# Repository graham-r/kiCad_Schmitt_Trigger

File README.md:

# kiCad_Schmitt_Trigger
Schmitt Trigger switch-bounce removal based kiCad projects

Rotary encoders and pushbutton (momentary) switches are prone to 'switch contact bounce' which may be
prolonged, non existent, or intermittent. This makes using these devices with micro-controllers 
(Arduino/Pico/STM.etc) difficult - usually requiring a software debounce method to make them usable.

Software methods can be made effective but they do take up clock cycles which can be a problem on 
micro-controllers with limited resources. In addition using them with interrupts can lead to interrupt cascades.

A hardware based solution is considered to be the best method of solving the problem, the basic electronic circuits
were designed by Jack G, Ganssle and also the subject of several videos by Ralph S Bacon. The kiCad schematics, PCB's 
etc were created by me.

Designs based on the Texas Instruments SN74AC14 Hex Schmitt Inverters or the Texas Instruments
SN74LVC3G17 Triple Schmitt-Trigger Buffer IC's.

The SN74AC14 is a through hole 14 pin DIP IC, and the SN74LVC3G17 is an 8 pin SMT IC.

Both devices are used with through hole and/or SMT resistors/capacitors/diodes as approopriate.

kiCad Projects with Panel/Hole Mount are designed to fit onto the back of a PEC11/12 rotary encoder.

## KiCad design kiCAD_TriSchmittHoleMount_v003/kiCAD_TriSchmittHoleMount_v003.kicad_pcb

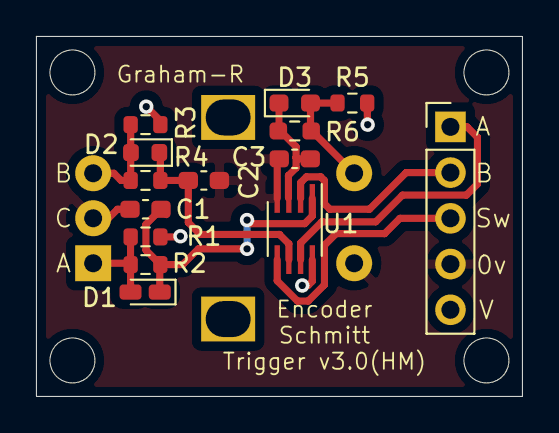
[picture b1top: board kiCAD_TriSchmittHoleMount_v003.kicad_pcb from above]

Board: 2 copper layers, 27.0 x 20.0 mm, 19 parts (1 on the bottom side), 11 nets.

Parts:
C1, C2, C3: 100nF; C_0603_1608Metric_Pad1.08x0.95mm_HandSolder
D1: 1N4148; D_0603_1608Metric_Castellated
D2: 1N4148; D_0603_1608Metric
D3: 1N4148; D_0603_1608Metric_Pad1.05x0.95mm_HandSolder
H4, H4#2, H4#3, H4#4: MountingHole; MountingHole_2.5mm_M2.5_ISO7380_no_courtyard
J1: Interface; PinHeader_1x05_P2.54mm_Vertical
R1, R3, R5: 82K; R_0603_1608Metric
R2, R4: 18K2; R_0603_1608Metric
R6: 18K2; R_0603_1608Metric_Pad0.98x0.95mm_HandSolder
SW1: Rotary_Encoder_EncSwitch; RotaryEncoder_Alps_EC12E-Switch_Vertical_H20mm
U1: 74LVC3G14; SSOP-8_2.95x2.8mm_P0.65mm

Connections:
/EncA_Out: J1.1, U1.7
/EncB_Out: J1.2, U1.2
/EncSw_Out: J1.3, U1.5
GND: C1.1, C2.1, C3.1, J1.4, SW1.C, SW1.S1, U1.4
Sig_EncA: D1.2, R1.1, R2.2, SW1.A
Sig_EncB: D2.2, R3.1, R4.2, SW1.B
Sig_EncSw: D3.2, R5.1, R6.2, SW1.S2
Trig_EncA: C1.2, D1.1, R2.1, U1.1
Trig_EncB: C2.2, D2.1, R4.1, U1.6
Trig_EncSw: C3.2, D3.1, R6.1, U1.3
VCC: J1.5, R1.2, R3.2, R5.2, U1.8

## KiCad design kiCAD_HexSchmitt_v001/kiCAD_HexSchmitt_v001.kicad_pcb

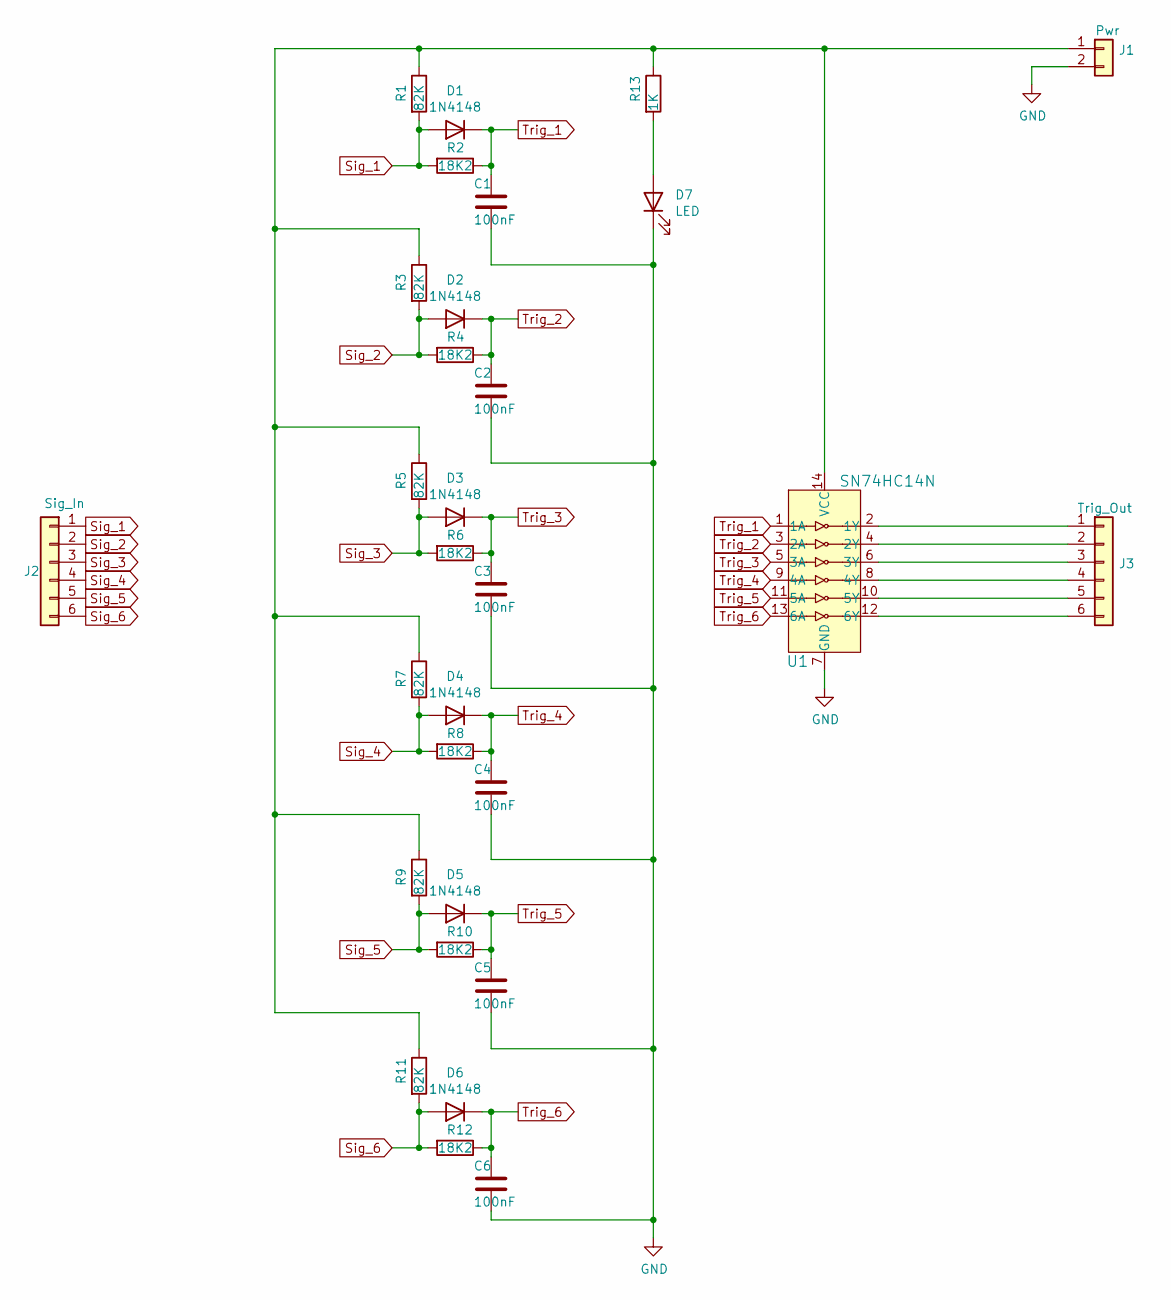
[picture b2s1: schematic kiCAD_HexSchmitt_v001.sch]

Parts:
C1, C2, C3, C4, C5, C6: 100nF; C_Disc_D5.0mm_W2.5mm_P5.00mm
D1, D2, D3, D4, D5, D6: 1N4148; D_DO-35_SOD27_P7.62mm_Horizontal
D7: LED; LED_D3.0mm
J1: Pwr; Molex_KK-254_AE-6410-02A_1x02_P2.54mm_Vertical
J2: Sig_In; Molex_KK-254_AE-6410-06A_1x06_P2.54mm_Vertical
J3: Trig_Out; Molex_KK-254_AE-6410-06A_1x06_P2.54mm_Vertical
R1, R3, R5, R7, R9, R11: 82K; R_Axial_DIN0207_L6.3mm_D2.5mm_P7.62mm_Horizontal
R2, R4, R6, R8, R10, R12: 18K2; R_Axial_DIN0207_L6.3mm_D2.5mm_P7.62mm_Horizontal
R13: 1K; R_Axial_DIN0207_L6.3mm_D2.5mm_P5.08mm_Vertical
U1: SN74HC14N; DIP-14_W3mm; MPN SN74HC14N; Digi-Key_PN 296-1577-5-ND

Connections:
GND: C1.2, C2.2, C3.2, C4.2, C5.2, C6.2, D7.1 (K), J1.2, U1.7 (GND)
unnamed: D7.2 (A), R13.2
unnamed: J1.1, R1.1, R3.1, R5.1, R7.1, R9.1, R11.1, R13.1, U1.14 (VCC)
unnamed: J3.1, U1.2 (1Y)
unnamed: J3.2, U1.4 (2Y)
unnamed: J3.3, U1.6 (3Y)
unnamed: J3.4, U1.8 (4Y)
unnamed: J3.5, U1.10 (5Y)
unnamed: J3.6, U1.12 (6Y)
Sig_1: D1.2 (A), J2.1, R1.2, R2.2
Sig_2: D2.2 (A), J2.2, R3.2, R4.2
Sig_3: D3.2 (A), J2.3, R5.2, R6.2
Sig_4: D4.2 (A), J2.4, R7.2, R8.2
Sig_5: D5.2 (A), J2.5, R9.2, R10.2
Sig_6: D6.2 (A), J2.6, R11.2, R12.2
Trig_1: C1.1, D1.1 (K), R2.1, U1.1 (1A)
Trig_2: C2.1, D2.1 (K), R4.1, U1.3 (2A)
Trig_3: C3.1, D3.1 (K), R6.1, U1.5 (3A)
Trig_4: C4.1, D4.1 (K), R8.1, U1.9 (4A)
Trig_5: C5.1, D5.1 (K), R10.1, U1.11 (5A)
Trig_6: C6.1, D6.1 (K), R12.1, U1.13 (6A)

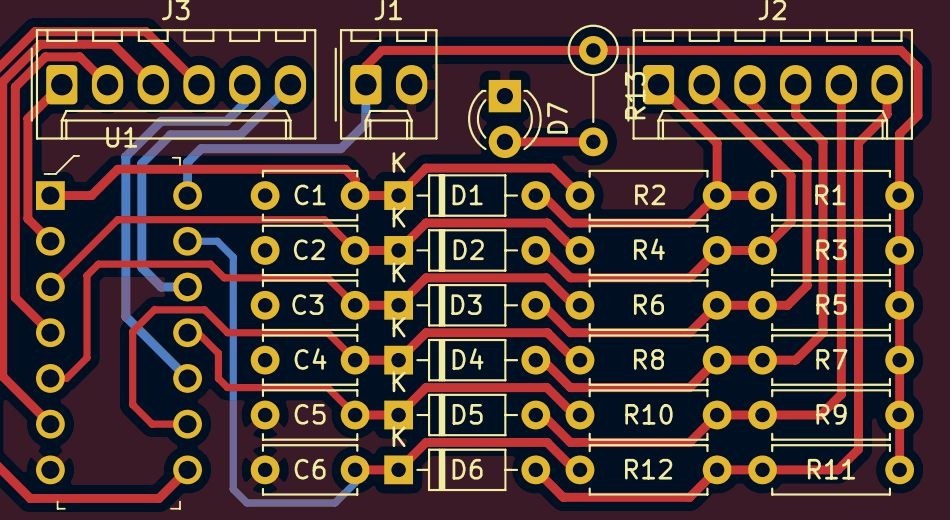
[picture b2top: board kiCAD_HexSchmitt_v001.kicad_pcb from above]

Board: 2 copper layers, 30 parts (0 on the bottom side), 21 nets.

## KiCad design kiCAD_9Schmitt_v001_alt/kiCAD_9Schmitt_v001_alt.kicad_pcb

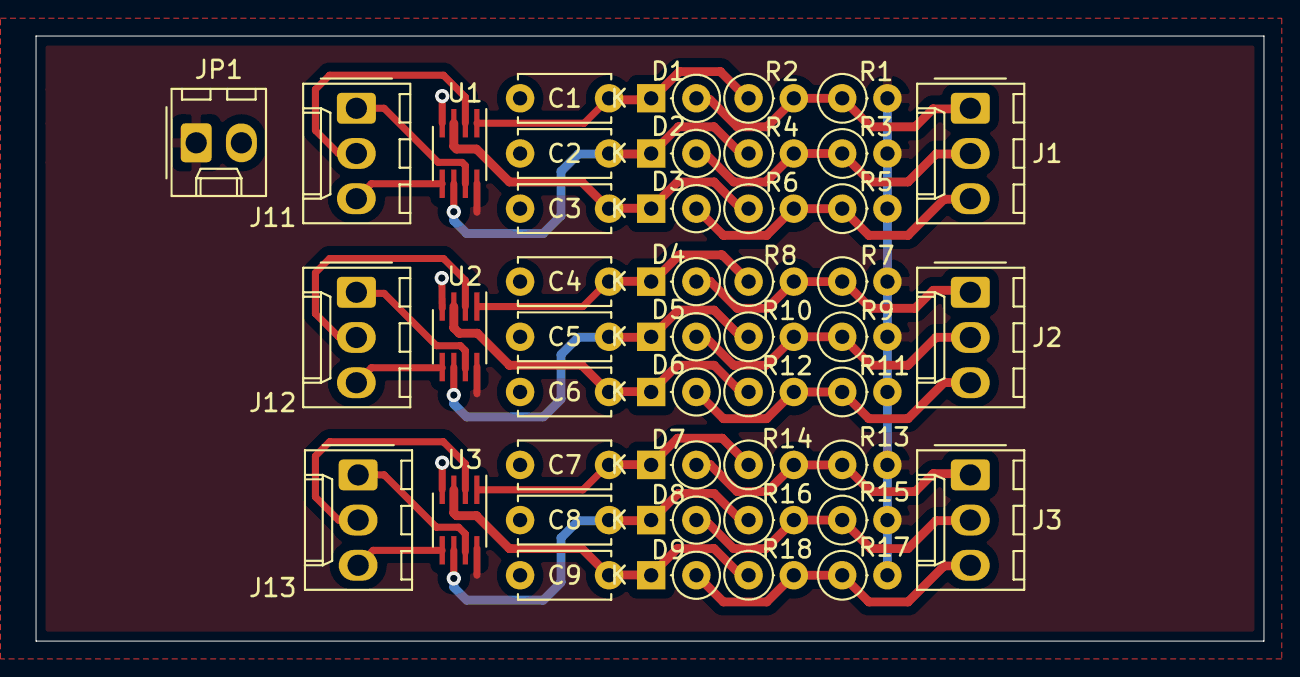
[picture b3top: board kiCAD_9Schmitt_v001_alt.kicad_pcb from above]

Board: 2 copper layers, 69.0 x 34.0 mm, 46 parts (0 on the bottom side), 29 nets.

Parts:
C1, C2, C3, C4, C5, C6, C7, C8, C9: 100nF; C_Disc_D5.0mm_W2.5mm_P5.00mm
D1, D2, D3, D4, D5, D6, D7, D8, D9: 1N4148; D_DO-35_SOD27_P2.54mm_Vertical_KathodeUp
J1, J2, J3: Sig_In; Molex_KK-254_AE-6410-03A_1x03_P2.54mm_Vertical
J11, J12, J13: Trig_Out; Molex_KK-254_AE-6410-03A_1x03_P2.54mm_Vertical
JP1: Pwr; Molex_KK-254_AE-6410-02A_1x02_P2.54mm_Vertical
R1, R3, R5, R7, R9, R11, R13, R15, R17: 82K; R_Axial_DIN0207_L6.3mm_D2.5mm_P2.54mm_Vertical
R2, R4, R6, R8, R10, R12, R14, R16, R18: 18K2; R_Axial_DIN0207_L6.3mm_D2.5mm_P2.54mm_Vertical
U1, U2, U3: 74LVC3G14_GR; SSOP-8_2.95x2.8mm_P0.65mm

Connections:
GND: C1.1, C2.1, C3.1, C4.1, C5.1, C6.1, C7.1, C8.1, C9.1, JP1.2, U1.4, U2.4, U3.4
unnamed: C1.2, D1.1, R2.1, U1.1
unnamed: C2.2, D2.1, R4.1, U1.6
unnamed: C3.2, D3.1, R6.1, U1.3
unnamed: C4.2, D4.1, R8.1, U2.1
unnamed: C5.2, D5.1, R10.1, U2.6
unnamed: C6.2, D6.1, R12.1, U2.3
unnamed: C7.2, D7.1, R14.1, U3.1
unnamed: C8.2, D8.1, R16.1, U3.6
unnamed: C9.2, D9.1, R18.1, U3.3
unnamed: D1.2, J1.1, R1.1, R2.2
unnamed: D2.2, J1.2, R3.1, R4.2
unnamed: D3.2, J1.3, R5.1, R6.2
unnamed: D4.2, J2.1, R7.1, R8.2
unnamed: D5.2, J2.2, R9.1, R10.2
unnamed: D6.2, J2.3, R11.1, R12.2
unnamed: D7.2, J3.1, R13.1, R14.2
unnamed: D8.2, J3.2, R15.1, R16.2
unnamed: D9.2, J3.3, R17.1, R18.2
unnamed: J11.1, U1.7
unnamed: J11.2, U1.2
unnamed: J11.3, U1.5
unnamed: J12.1, U2.7
unnamed: J12.2, U2.2
unnamed: J12.3, U2.5
unnamed: J13.1, U3.7
unnamed: J13.2, U3.2
unnamed: J13.3, U3.5
VCC: JP1.1, R1.2, R3.2, R5.2, R7.2, R9.2, R11.2, R13.2, R15.2, R17.2, U1.8, U2.8, U3.8

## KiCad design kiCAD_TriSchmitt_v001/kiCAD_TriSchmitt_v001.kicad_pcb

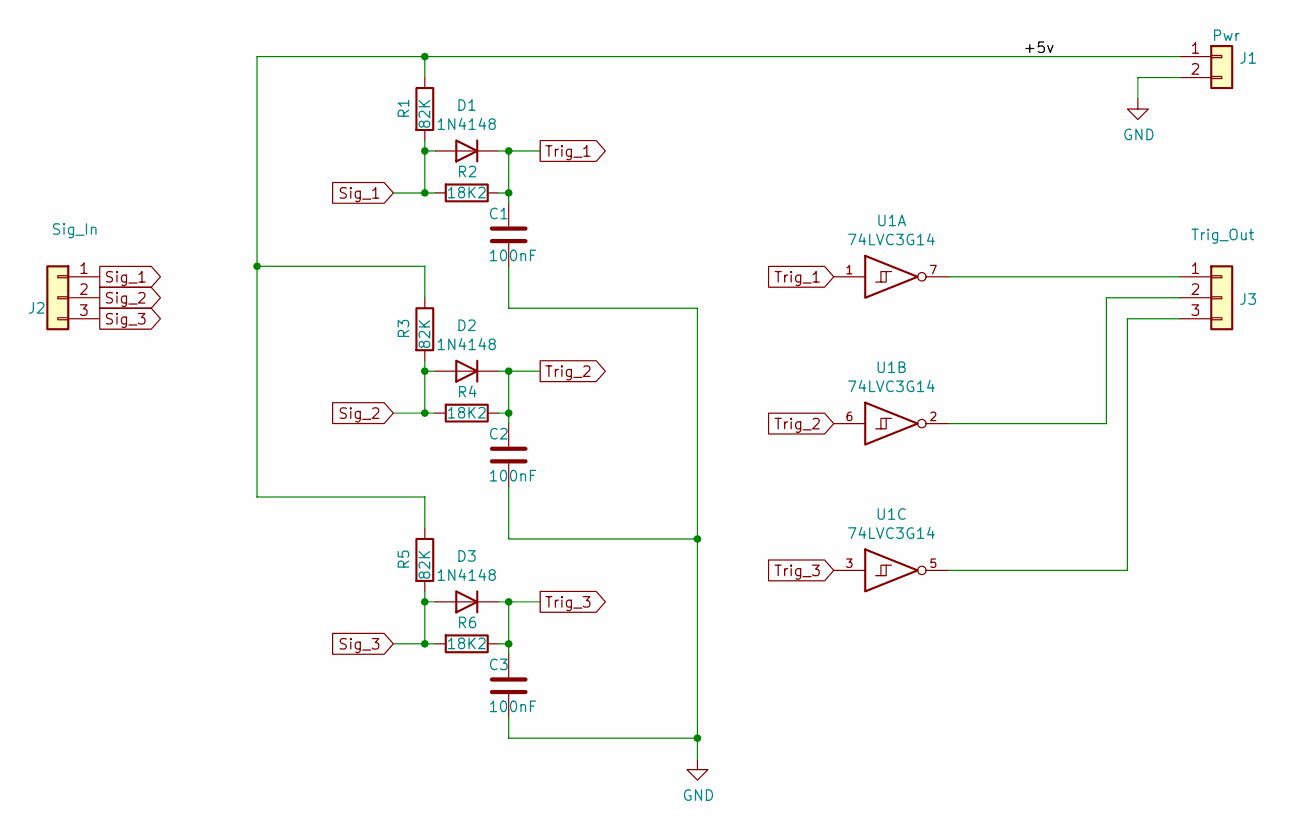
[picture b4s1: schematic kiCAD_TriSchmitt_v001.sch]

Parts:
C1, C2, C3: 100nF; C_Disc_D5.0mm_W2.5mm_P5.00mm
D1, D2, D3: 1N4148; D_DO-35_SOD27_P7.62mm_Horizontal
J1: Pwr; Molex_KK-254_AE-6410-02A_1x02_P2.54mm_Vertical
J2: Sig_In; Molex_KK-254_AE-6410-03A_1x03_P2.54mm_Vertical
J3: Trig_Out; Molex_KK-254_AE-6410-03A_1x03_P2.54mm_Vertical
R1, R3, R5: 82K; R_Axial_DIN0207_L6.3mm_D2.5mm_P7.62mm_Horizontal
R2, R4, R6: 18K2; R_Axial_DIN0207_L6.3mm_D2.5mm_P7.62mm_Horizontal
U1: 74LVC3G14; SSOP-8_2.95x2.8mm_P0.65mm

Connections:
/+5v: J1.1, R1.1, R3.1, R5.1
GND: C1.2, C2.2, C3.2, J1.2, U1.4 (GND)
unnamed: J3.1, U1.7
unnamed: J3.2, U1.2
unnamed: J3.3, U1.5
Sig_1: D1.2 (A), J2.1, R1.2, R2.2
Sig_2: D2.2 (A), J2.2, R3.2, R4.2
Sig_3: D3.2 (A), J2.3, R5.2, R6.2
Trig_1: C1.1, D1.1 (K), R2.1, U1.1
Trig_2: C2.1, D2.1 (K), R4.1, U1.6
Trig_3: C3.1, D3.1 (K), R6.1, U1.3
VCC: U1.8 (VCC)

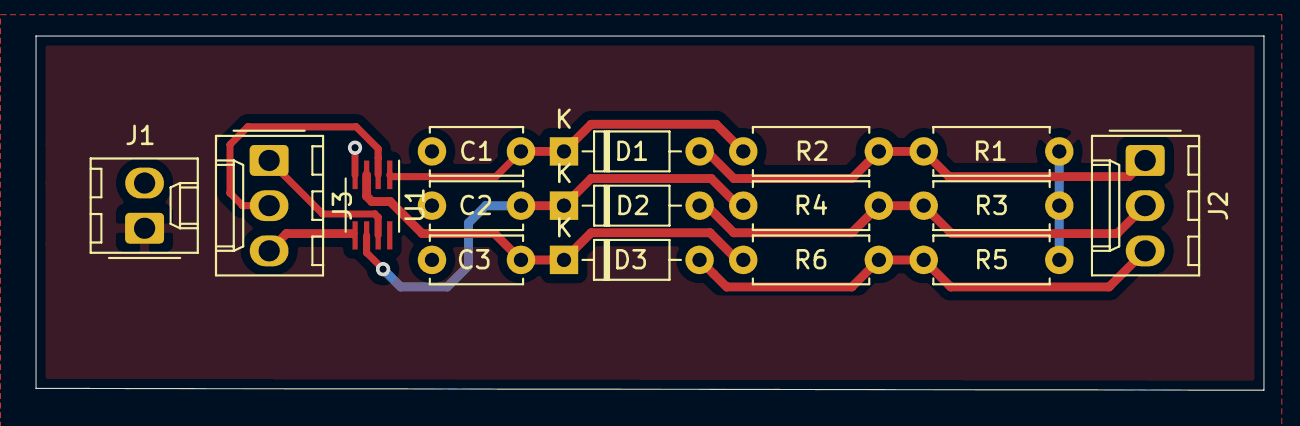
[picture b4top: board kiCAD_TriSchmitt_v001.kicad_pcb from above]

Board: 2 copper layers, 69.0 x 19.9 mm, 16 parts (0 on the bottom side), 11 nets.

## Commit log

2021-11-27 First upload of all Schmitt Trigger Debounce projects
